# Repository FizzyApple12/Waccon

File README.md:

# Waccon

This repo is right now still a work in progress, nothing has been finalized and things will probably be broken, stay tuned as things are finalized though!

If you'd like to test out the current firmware on your own hardware, there are 2 github actions scripts for the Touch Panel firmware and the Protocol Translator firmware

The 6 Touch Panel firmware builds correspond to which position you want the Touch Panel to be in (1 being top, 6 being bottom)

The 4 Protocol Translator firmware builds correspond to if the translator is controlling the left or right of the controller and if you want to mirror Touch Panel 1's inputs to all 6 Touch Panels

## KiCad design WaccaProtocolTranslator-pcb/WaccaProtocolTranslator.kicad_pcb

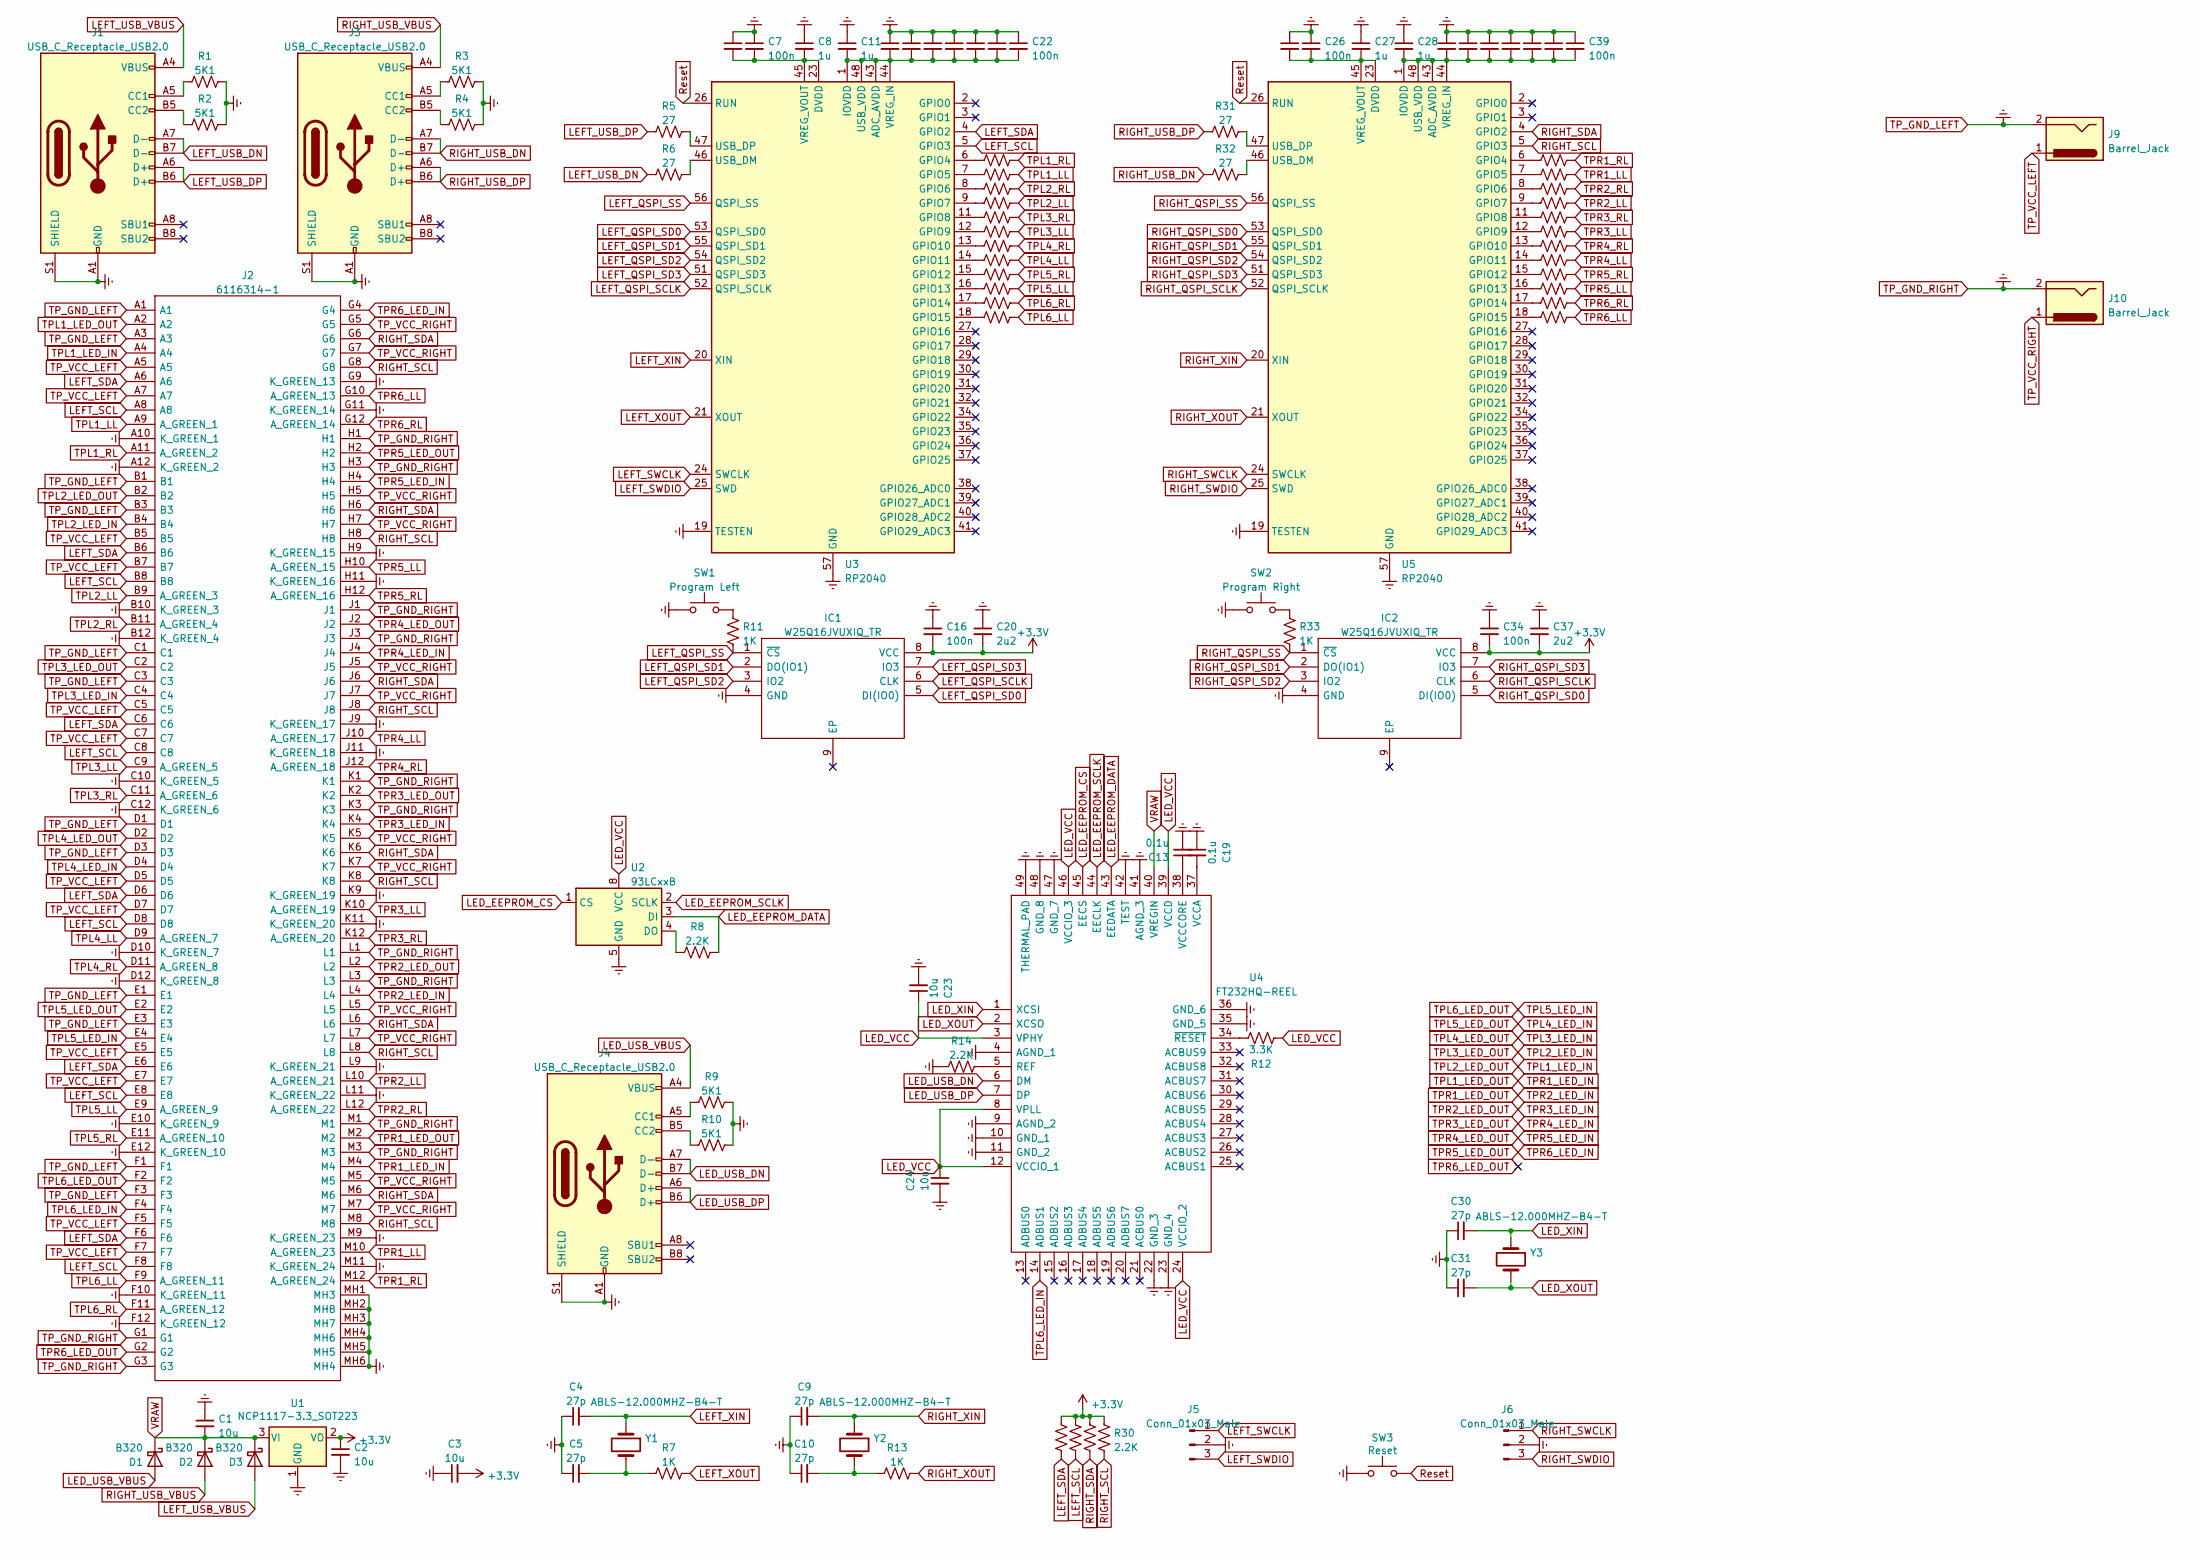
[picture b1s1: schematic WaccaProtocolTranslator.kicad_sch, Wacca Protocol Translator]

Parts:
C1, C2, C3, C23, C24: 10u; C_0402_1005Metric
C4, C5, C9, C10, C30, C31: 27p; C_0402_1005Metric
C6, C7, C12, C14, C15, C16, C17, C18, C21, C22, C25, C26, C29, C32, C33, C34, C35, C36, C38, C39: 100n; C_0402_1005Metric
C8, C11, C27, C28: 1u; C_0402_1005Metric
C13, C19: 0.1u; C_0402_1005Metric
C20, C37: 2u2; C_0402_1005Metric
D1, D2, D3: B320; D_SMC
IC1, IC2: W25Q16JVUXIQ_TR; SON50P300X200X60-9N; Manufacturer_Part_Number W25Q16JVUXIQ TR; Mouser Part Number 454-W25Q16JVUXIQTR
J1, J3, J4: USB_C_Receptacle_USB2.0; USB_C_Receptacle_Amphenol_12401548E4-2A
J2: 6116314-1; 61163141; Mouser Part Number 571-6116314-1
J5, J6: Conn_01x03_Male; PinHeader_1x03_P2.54mm_Vertical
J9, J10: Barrel_Jack; BarrelJack_CUI_PJ-063AH_Horizontal
R1, R2, R3, R4, R9, R10: 5K1; R_0402_1005Metric
R5, R6, R31, R32: 27; R_0402_1005Metric
R7, R11, R13, R33: 1K; R_0402_1005Metric
R8, R14, R27, R28, R29, R30: 2.2K; R_0402_1005Metric
R12: 3.3K; R_0402_1005Metric
R15, R16, R17, R18, R19, R20, R21, R22, R23, R24, R25, R26, R34, R35, R36, R37, R38, R39, R40, R41, R42, R43, R44, R45: 150; R_0402_1005Metric
SW1: Program Left; SW_SPST_B3U-1000P
SW2: Program Right; SW_SPST_B3U-1000P
SW3: Reset; SW_SPST_B3U-1000P
U1: NCP1117-3.3_SOT223; SOT-223-3_TabPin2
U2: 93LCxxB; SOP65P490X110-8N
U3, U5: RP2040; QFN-56-1EP_7x7mm_P0.4mm_EP3.2x3.2mm
U4: FT232HQ-REEL; QFN50P800X800X100-49N-D; Mouser Part Number 895-FT232HQ-REEL
Y1, Y2, Y3: ABLS-12.000MHZ-B4-T; Crystal_HC49-4H_Vertical

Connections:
+3.3V: C2.1, C3.2, C16.2, C20.2, C34.2, C37.2, IC1.8 (VCC), IC2.8 (VCC), R27.2, R28.2, R29.2, R30.2, U1.2 (VO)
LED_EEPROM_CS: U2.1 (CS), U4.45 (EECS)
LED_EEPROM_DATA: R8.2, U2.3 (DI), U4.43 (EEDATA)
LED_EEPROM_SCLK: U2.2 (SCLK), U4.44 (EECLK)
LED_USB_DN: J4.A7 (D-), J4.B7 (D-), U4.6 (DM)
LED_USB_DP: J4.A6 (D+), J4.B6 (D+), U4.7 (DP)
LED_USB_VBUS: D1.2 (A), J4.A4 (VBUS), J4.A9 (VBUS), J4.B4 (VBUS), J4.B9 (VBUS)
LED_VCC: C23.1, C24.1, R12.1, U2.8 (VCC), U4.3 (VPHY), U4.8 (VPLL), U4.12 (VCCIO_1), U4.24 (VCCIO_2), U4.39 (VCCD), U4.46 (VCCIO_3)
LED_XIN: C30.2, U4.1 (XCSI), Y3.1
LED_XOUT: C31.2, U4.2 (XCSO), Y3.2
LEFT_QSPI_SCLK: IC1.6 (CLK), U3.52 (QSPI_SCLK)
LEFT_QSPI_SD0: IC1.5 (DI(IO0)), U3.53 (QSPI_SD0)
LEFT_QSPI_SD1: IC1.2 (DO(IO1)), U3.55 (QSPI_SD1)
LEFT_QSPI_SD2: IC1.3 (IO2), U3.54 (QSPI_SD2)
LEFT_QSPI_SD3: IC1.7 (IO3), U3.51 (QSPI_SD3)
LEFT_QSPI_SS: IC1.1 (~CS), R11.2, U3.56 (QSPI_SS)
LEFT_SCL: J2.A8, J2.B8, J2.C8, J2.D8, J2.E8, J2.F8, R28.1, U3.5 (GPIO3)
LEFT_SDA: J2.A6, J2.B6, J2.C6, J2.D6, J2.E6, J2.F6, R27.1, U3.4 (GPIO2)
LEFT_SWCLK: J5.1, U3.24 (SWCLK)
LEFT_SWDIO: J5.3, U3.25 (SWD)
LEFT_USB_DN: J1.A7 (D-), J1.B7 (D-), R6.1
LEFT_USB_DP: J1.A6 (D+), J1.B6 (D+), R5.1
LEFT_USB_VBUS: D3.2 (A), J1.A4 (VBUS), J1.A9 (VBUS), J1.B4 (VBUS), J1.B9 (VBUS)
LEFT_XIN: C4.2, U3.20 (XIN), Y1.1
LEFT_XOUT: R7.2, U3.21 (XOUT)
unnamed: C5.2, R7.1, Y1.2
unnamed: C10.2, R13.1, Y2.2
unnamed: J1.A5 (CC1), R1.1
unnamed: J1.B5 (CC2), R2.1
unnamed: J3.A5 (CC1), R3.1
unnamed: J3.B5 (CC2), R4.1
unnamed: J4.A5 (CC1), R9.1
unnamed: J4.B5 (CC2), R10.1
unnamed: R11.1, SW1.2
unnamed: R33.1, SW2.2
unnamed: R8.1, U2.4 (DO)
unnamed: C11.2, C12.2, C14.2, C15.2, C17.2, C18.2, C21.2, C22.2, U3.1 (IOVDD), U3.10 (IOVDD), U3.22 (IOVDD), U3.33 (IOVDD), U3.42 (IOVDD), U3.43 (ADC_AVDD), U3.44 (VREG_IN), U3.48 (USB_VDD), U3.49 (IOVDD)
unnamed: R16.1, U3.6 (GPIO4)
unnamed: R15.1, U3.7 (GPIO5)
unnamed: R18.1, U3.8 (GPIO6)
unnamed: R17.1, U3.9 (GPIO7)
unnamed: R20.1, U3.11 (GPIO8)
unnamed: R19.1, U3.12 (GPIO9)
unnamed: R22.1, U3.13 (GPIO10)
unnamed: R21.1, U3.14 (GPIO11)
unnamed: R24.1, U3.15 (GPIO12)
unnamed: R23.1, U3.16 (GPIO13)
unnamed: R26.1, U3.17 (GPIO14)
unnamed: R25.1, U3.18 (GPIO15)
unnamed: R6.2, U3.46 (USB_DM)
unnamed: R5.2, U3.47 (USB_DP)
unnamed: C6.2, C7.2, C8.2, U3.23 (DVDD), U3.45 (VREG_VOUT), U3.50 (DVDD)
unnamed: R14.2, U4.5 (REF)
unnamed: C19.2, U4.37 (VCCA)
unnamed: C13.1, U4.38 (VCCCORE)
unnamed: R12.2, U4.34 (~RESET)
unnamed: C28.2, C29.2, C32.2, C33.2, C35.2, C36.2, C38.2, C39.2, U5.1 (IOVDD), U5.10 (IOVDD), U5.22 (IOVDD), U5.33 (IOVDD), U5.42 (IOVDD), U5.43 (ADC_AVDD), U5.44 (VREG_IN), U5.48 (USB_VDD), U5.49 (IOVDD)
unnamed: R35.1, U5.6 (GPIO4)
unnamed: R34.1, U5.7 (GPIO5)
unnamed: R37.1, U5.8 (GPIO6)
unnamed: R36.1, U5.9 (GPIO7)
unnamed: R39.1, U5.11 (GPIO8)
unnamed: R38.1, U5.12 (GPIO9)
unnamed: R41.1, U5.13 (GPIO10)
unnamed: R40.1, U5.14 (GPIO11)
unnamed: R43.1, U5.15 (GPIO12)
unnamed: R42.1, U5.16 (GPIO13)
unnamed: R45.1, U5.17 (GPIO14)
unnamed: R44.1, U5.18 (GPIO15)
unnamed: R32.2, U5.46 (USB_DM)
unnamed: R31.2, U5.47 (USB_DP)
unnamed: C25.2, C26.2, C27.2, U5.23 (DVDD), U5.45 (VREG_VOUT), U5.50 (DVDD)
RIGHT_QSPI_SCLK: IC2.6 (CLK), U5.52 (QSPI_SCLK)
RIGHT_QSPI_SD0: IC2.5 (DI(IO0)), U5.53 (QSPI_SD0)
RIGHT_QSPI_SD1: IC2.2 (DO(IO1)), U5.55 (QSPI_SD1)
RIGHT_QSPI_SD2: IC2.3 (IO2), U5.54 (QSPI_SD2)
RIGHT_QSPI_SD3: IC2.7 (IO3), U5.51 (QSPI_SD3)
RIGHT_QSPI_SS: IC2.1 (~CS), R33.2, U5.56 (QSPI_SS)
RIGHT_SCL: J2.G8, J2.H8, J2.J8, J2.K8, J2.L8, J2.M8, R30.1, U5.5 (GPIO3)
RIGHT_SDA: J2.G6, J2.H6, J2.J6, J2.K6, J2.L6, J2.M6, R29.1, U5.4 (GPIO2)
RIGHT_SWCLK: J6.1, U5.24 (SWCLK)
RIGHT_SWDIO: J6.3, U5.25 (SWD)
RIGHT_USB_DN: J3.A7 (D-), J3.B7 (D-), R32.1
RIGHT_USB_DP: J3.A6 (D+), J3.B6 (D+), R31.1
RIGHT_USB_VBUS: D2.2 (A), J3.A4 (VBUS), J3.A9 (VBUS), J3.B4 (VBUS), J3.B9 (VBUS)
RIGHT_XIN: C9.2, U5.20 (XIN), Y2.1
RIGHT_XOUT: R13.2, U5.21 (XOUT)
Reset: SW3.2, U3.26 (RUN), U5.26 (RUN)
TPL1_LED_IN: J2.A4, J2.B2
TPL1_LED_OUT: J2.A2, J2.M4
TPL1_LL: J2.A9 (A_GREEN_1), R15.2
TPL1_RL: J2.A11 (A_GREEN_2), R16.2
TPL2_LED_IN: J2.B4, J2.C2
TPL2_LL: J2.B9 (A_GREEN_3), R17.2
TPL2_RL: J2.B11 (A_GREEN_4), R18.2
TPL3_LED_IN: J2.C4, J2.D2
TPL3_LL: J2.C9 (A_GREEN_5), R19.2
TPL3_RL: J2.C11 (A_GREEN_6), R20.2
TPL4_LED_IN: J2.D4, J2.E2
TPL4_LL: J2.D9 (A_GREEN_7), R21.2
TPL4_RL: J2.D11 (A_GREEN_8), R22.2
TPL5_LED_IN: J2.E4, J2.F2
TPL5_LL: J2.E9 (A_GREEN_9), R23.2
TPL5_RL: J2.E11 (A_GREEN_10), R24.2
TPL6_LED_IN: J2.F4, U4.14 (ADBUS1)
TPL6_LL: J2.F9 (A_GREEN_11), R25.2
TPL6_RL: J2.F11 (A_GREEN_12), R26.2
TPR1_LED_OUT: J2.L4, J2.M2
TPR1_LL: J2.M10 (A_GREEN_23), R34.2
TPR1_RL: J2.M12 (A_GREEN_24), R35.2
TPR2_LED_OUT: J2.K4, J2.L2
TPR2_LL: J2.L10 (A_GREEN_21), R36.2
TPR2_RL: J2.L12 (A_GREEN_22), R37.2
TPR3_LED_OUT: J2.J4, J2.K2
TPR3_LL: J2.K10 (A_GREEN_19), R38.2
TPR3_RL: J2.K12 (A_GREEN_20), R39.2
TPR4_LED_OUT: J2.H4, J2.J2
TPR4_LL: J2.J10 (A_GREEN_17), R40.2
TPR4_RL: J2.J12 (A_GREEN_18), R41.2
TPR5_LED_OUT: J2.G4, J2.H2
TPR5_LL: J2.H10 (A_GREEN_15), R42.2
TPR5_RL: J2.H12 (A_GREEN_16), R43.2
TPR6_LED_OUT: J2.G2
TPR6_LL: J2.G10 (A_GREEN_13), R44.2
TPR6_RL: J2.G12 (A_GREEN_14), R45.2
TP_GND_LEFT: C1.1, C2.2, C3.1, C4.1, C5.1, C6.1, C7.1, C8.1, C9.1, C10.1, C11.1, C12.1, C13.2, C14.1, C15.1, C16.1, C17.1, C18.1, C19.1, C20.1, C21.1, C22.1, C23.2, C24.2, C25.1, C26.1, C27.1, C28.1, C29.1, C30.1, C31.1, C32.1, C33.1, C34.1, C35.1, C36.1, C37.1, C38.1, C39.1, IC1.4 (GND), IC2.4 (GND), J1.A1 (GND), J1.A12 (GND), J1.B1 (GND), J1.B12 (GND), J1.S1 (SHIELD), J2.A1, J2.A3, J2.A10 (K_GREEN_1), J2.A12 (K_GREEN_2), J2.B1, J2.B3, J2.B10 (K_GREEN_3), J2.B12 (K_GREEN_4), J2.C1, J2.C3, J2.C10 (K_GREEN_5), J2.C12 (K_GREEN_6), J2.D1, J2.D3, J2.D10 (K_GREEN_7), J2.D12 (K_GREEN_8), J2.E1, J2.E3, J2.E10 (K_GREEN_9), J2.E12 (K_GREEN_10), J2.F1, J2.F3, J2.F10 (K_GREEN_11), J2.F12 (K_GREEN_12), J2.G1, J2.G3, J2.G9 (K_GREEN_13), J2.G11 (K_GREEN_14), J2.H1, J2.H3, J2.H9 (K_GREEN_15), J2.H11 (K_GREEN_16), J2.J1, J2.J3, J2.J9 (K_GREEN_17), J2.J11 (K_GREEN_18), J2.K1, J2.K3, J2.K9 (K_GREEN_19), J2.K11 (K_GREEN_20), J2.L1, J2.L3, J2.L9 (K_GREEN_21), J2.L11 (K_GREEN_22), J2.M1, J2.M3, J2.M9 (K_GREEN_23), J2.M11 (K_GREEN_24), J2.MH1 (MH3), J2.MH2 (MH8), J2.MH3 (MH7), J2.MH4 (MH6), J2.MH5, J2.MH6 (MH4), J3.A1 (GND), J3.A12 (GND), J3.B1 (GND), J3.B12 (GND), J3.S1 (SHIELD), J4.A1 (GND), J4.A12 (GND), J4.B1 (GND), J4.B12 (GND), J4.S1 (SHIELD), J5.2, J6.2, J9.2, J10.2, R1.2, R2.2, R3.2, R4.2, R9.2, R10.2, R14.1, SW1.1, SW2.1, SW3.1, U1.1 (GND), U2.5 (GND), U3.19 (TESTEN), U3.57 (GND), U4.4 (AGND_1), U4.9 (AGND_2), U4.10 (GND_1), U4.11 (GND_2), U4.22 (GND_3), U4.23 (GND_4), U4.35 (GND_5), U4.36 (GND_6), U4.41 (AGND_3), U4.42 (TEST), U4.47 (GND_7), U4.48 (GND_8), U4.49 (THERMAL_PAD), U5.19 (TESTEN), U5.57 (GND)
TP_VCC_LEFT: J2.A5, J2.A7, J2.B5, J2.B7, J2.C5, J2.C7, J2.D5, J2.D7, J2.E5, J2.E7, J2.F5, J2.F7, J9.1
TP_VCC_RIGHT: J2.G5, J2.G7, J2.H5, J2.H7, J2.J5, J2.J7, J2.K5, J2.K7, J2.L5, J2.L7, J2.M5, J2.M7, J10.1
VRAW: C1.2, D1.1 (K), D2.1 (K), D3.1 (K), U1.3 (VI), U4.40 (VREGIN)

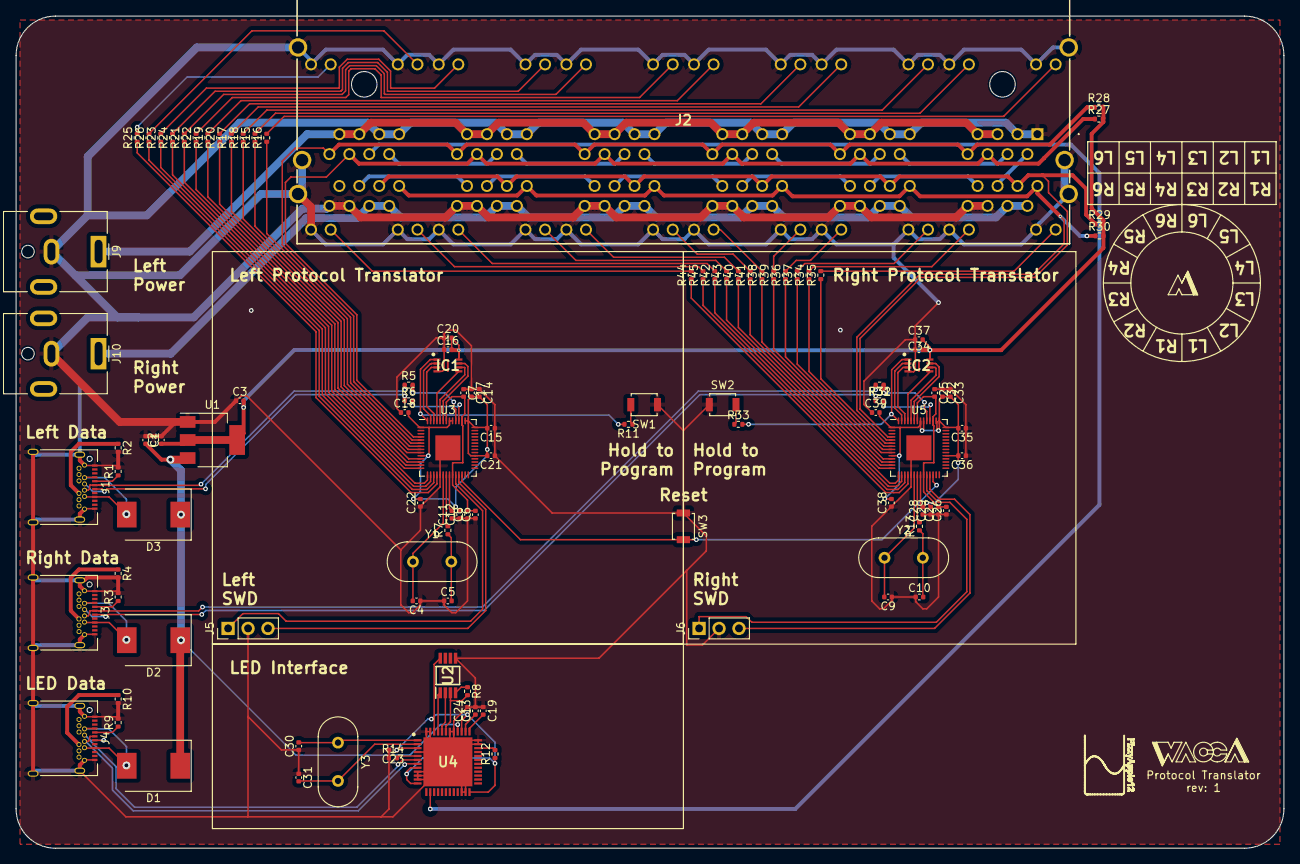
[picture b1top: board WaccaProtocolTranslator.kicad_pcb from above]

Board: 2 copper layers, 161.5 x 106.0 mm, 108 parts (0 on the bottom side), 128 nets.

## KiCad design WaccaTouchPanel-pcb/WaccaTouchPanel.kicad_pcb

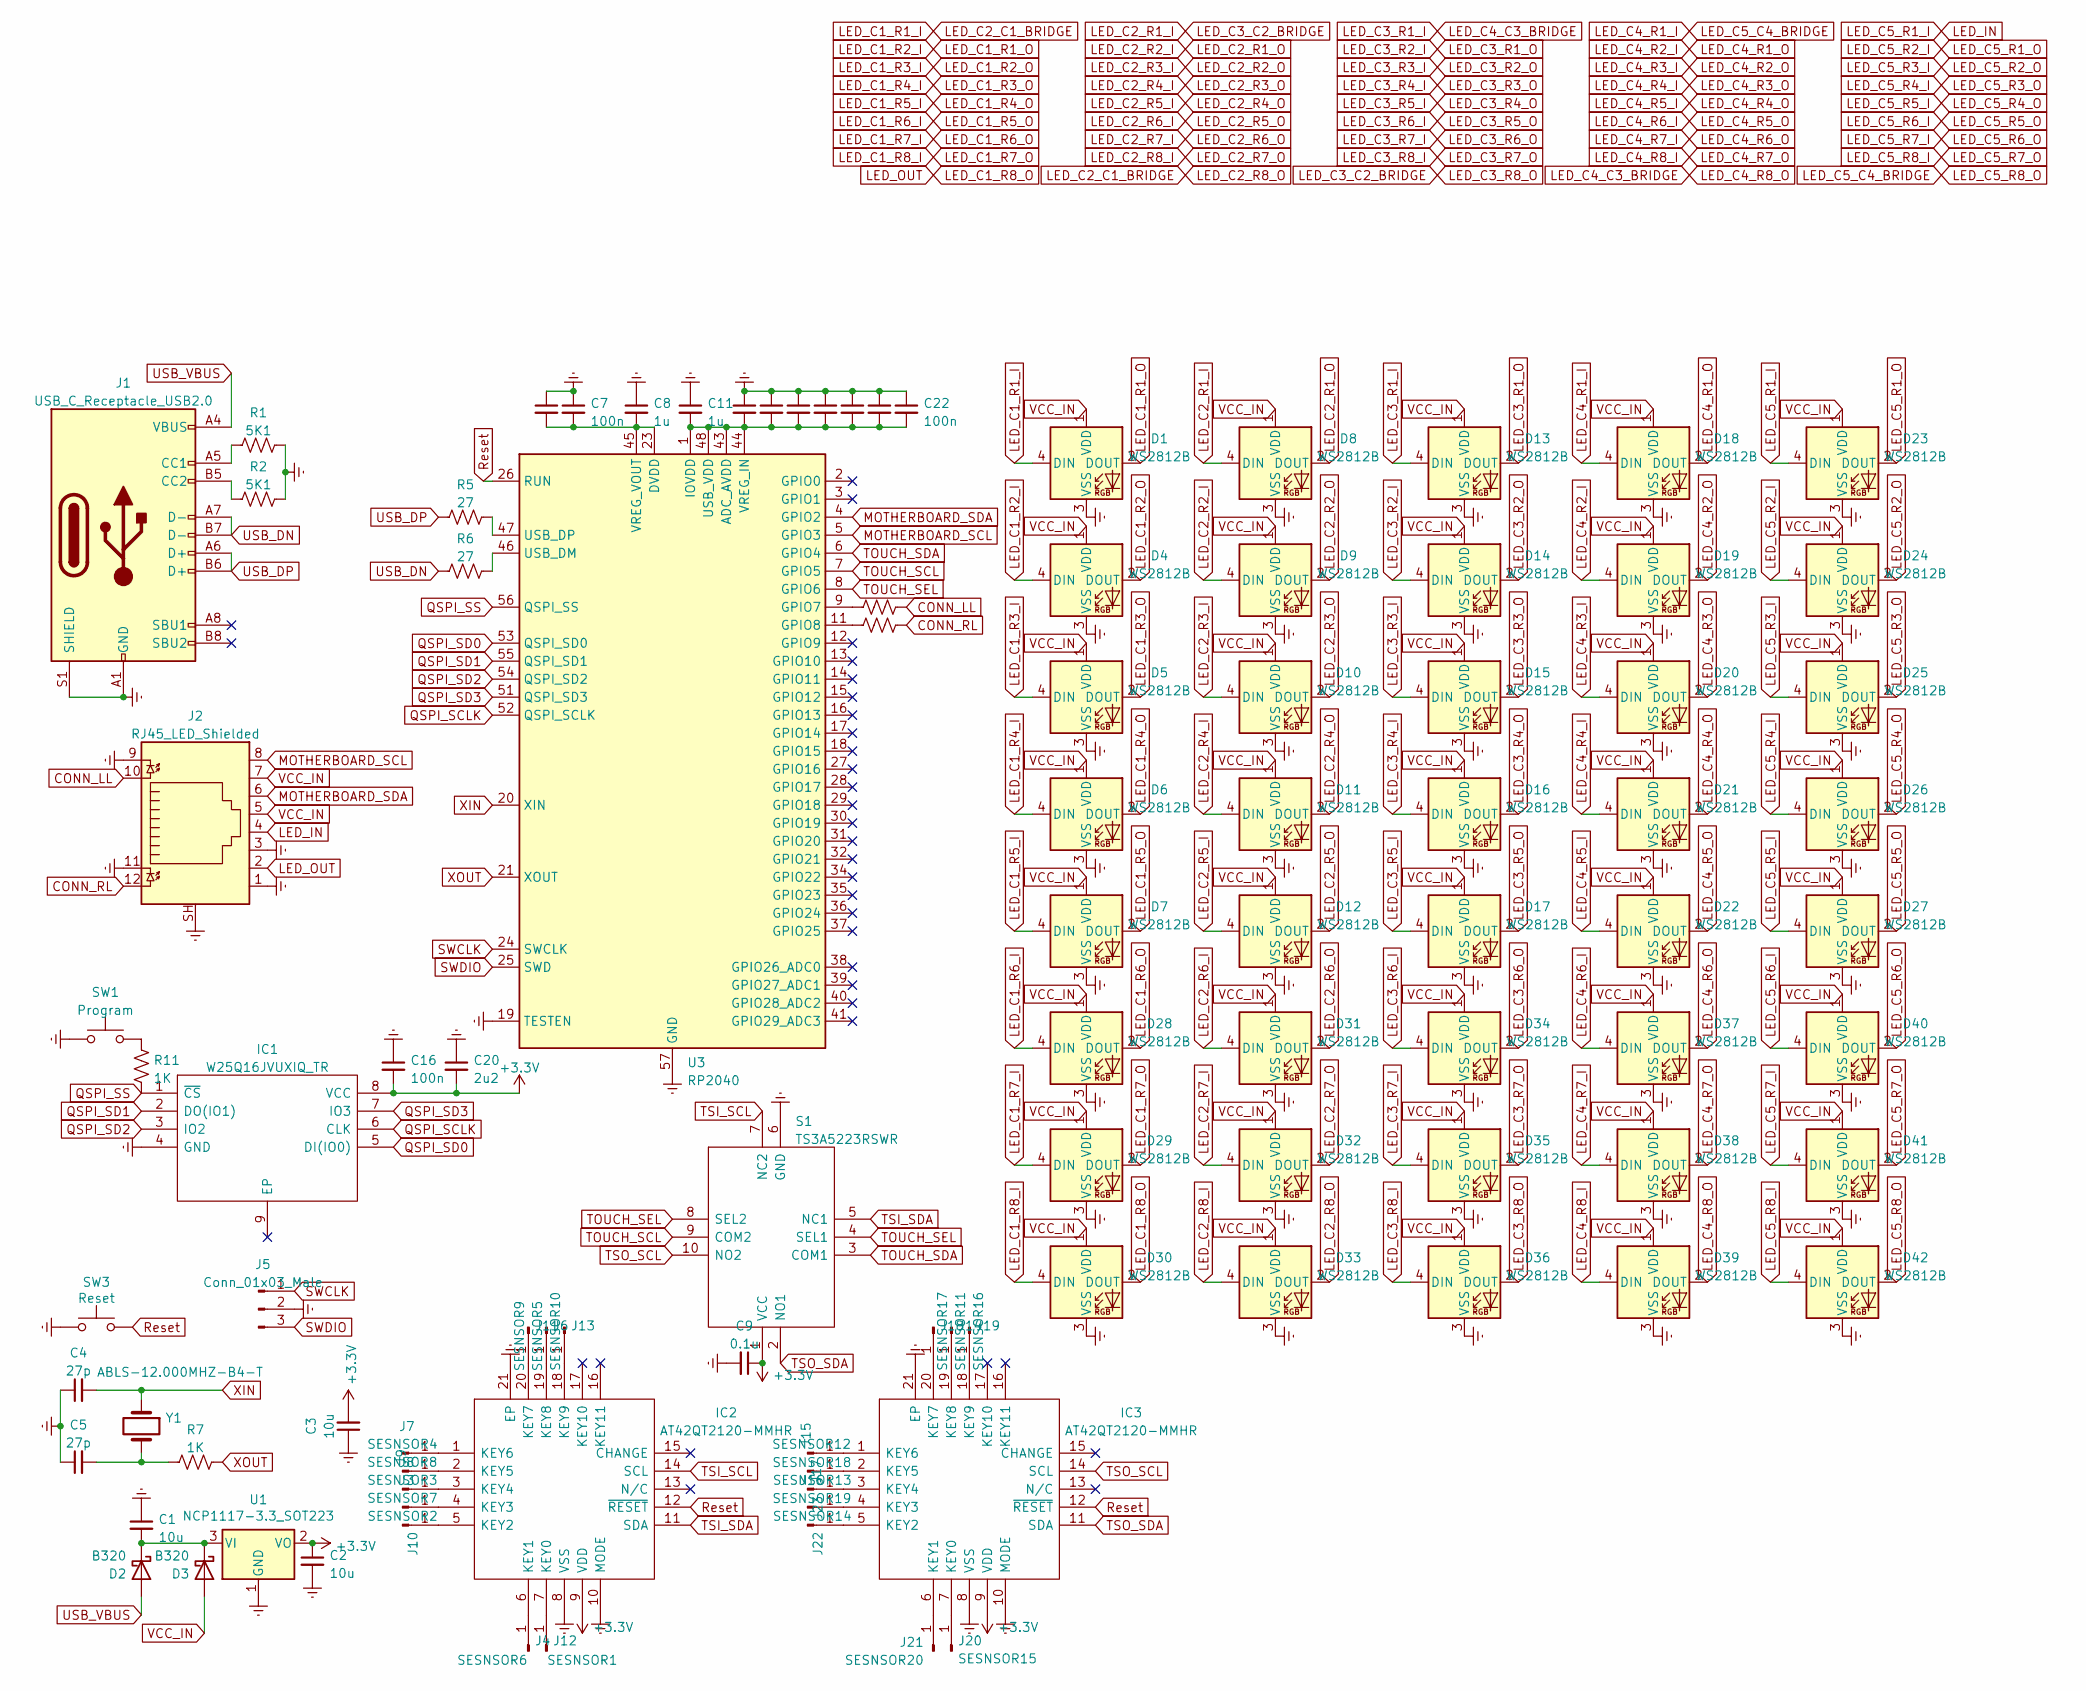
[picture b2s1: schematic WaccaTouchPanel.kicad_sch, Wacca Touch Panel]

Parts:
C1, C2, C3: 10u; C_0402_1005Metric
C4, C5: 27p; C_0402_1005Metric
C6, C7, C12, C14, C15, C16, C17, C18, C21, C22: 100n; C_0402_1005Metric
C8, C11: 1u; C_0402_1005Metric
C9: 0.1u; C_0402_1005Metric
C20: 2u2; C_0402_1005Metric
D1, D4, D5, D6, D7, D8, D9, D10, D11, D12, D13, D14, D15, D16, D17, D18, D19, D20, D21, D22, D23, D24, D25, D26, D27, D28, D29, D30, D31, D32, D33, D34, D35, D36, D37, D38, D39, D40, D41, D42: WS2812B; LED_WS2812B_PLCC4_5.0x5.0mm_P3.2mm
D2, D3: B320; D_SMC
IC1: W25Q16JVUXIQ_TR; SON50P300X200X60-9N; Manufacturer_Part_Number W25Q16JVUXIQ TR; Mouser Part Number 454-W25Q16JVUXIQTR
IC2, IC3: AT42QT2120-MMHR; QFN45P300X300X85-21N; Mouser Part Number 556-AT42QT2120-MMHR
J1: USB_C_Receptacle_USB2.0; USB_C_Receptacle_Amphenol_12401548E4-2A
J2: RJ45_LED_Shielded; RJ45_Amphenol_RJHSE538X
J3: SESNSOR7; PinHeader_1x01_P2.54mm_Vertical
J4: SESNSOR6; PinHeader_1x01_P2.54mm_Vertical
J5: Conn_01x03_Male; PinHeader_1x03_P2.54mm_Vertical
J6: SESNSOR5; PinHeader_1x01_P2.54mm_Vertical
J7: SESNSOR4; PinHeader_1x01_P2.54mm_Vertical
J8: SESNSOR3; PinHeader_1x01_P2.54mm_Vertical
J9: SESNSOR8; PinHeader_1x01_P2.54mm_Vertical
J10: SESNSOR2; PinHeader_1x01_P2.54mm_Vertical
J11: SESNSOR9; PinHeader_1x01_P2.54mm_Vertical
J12: SESNSOR1; PinHeader_1x01_P2.54mm_Vertical
J13: SESNSOR10; PinHeader_1x01_P2.54mm_Vertical
J14: SESNSOR11; PinHeader_1x01_P2.54mm_Vertical
J15: SESNSOR12; PinHeader_1x01_P2.54mm_Vertical
J16: SESNSOR19; PinHeader_1x01_P2.54mm_Vertical
J17: SESNSOR18; PinHeader_1x01_P2.54mm_Vertical
J18: SESNSOR17; PinHeader_1x01_P2.54mm_Vertical
J19: SESNSOR16; PinHeader_1x01_P2.54mm_Vertical
J20: SESNSOR15; PinHeader_1x01_P2.54mm_Vertical
J21: SESNSOR20; PinHeader_1x01_P2.54mm_Vertical
J22: SESNSOR14; PinHeader_1x01_P2.54mm_Vertical
J23: SESNSOR13; PinHeader_1x01_P2.54mm_Vertical
R1, R2: 5K1; R_0402_1005Metric
R5, R6: 27; R_0402_1005Metric
R7, R11: 1K; R_0402_1005Metric
R15, R16: 150; R_0402_1005Metric
S1: TS3A5223RSWR; RSW_RPUQFNN10_; Mouser Part Number 595-TS3A5223RSWR
SW1: Program; SW_SPST_B3U-1000P
SW3: Reset; SW_SPST_B3U-1000P
U1: NCP1117-3.3_SOT223; SOT-223-3_TabPin2
U3: RP2040; QFN-56-1EP_7x7mm_P0.4mm_EP3.2x3.2mm
Y1: ABLS-12.000MHZ-B4-T; Crystal_HC49-4H_Vertical

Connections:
+3.3V: C2.1, C3.2, C9.1, C16.2, C20.2, IC1.8 (VCC), IC2.9 (VDD), IC3.9 (VDD), S1.1 (VCC), U1.2 (VO)
CONN_LL: J2.10, R16.2
CONN_RL: J2.12, R15.2
Earth: C1.1, C2.2, C3.1, C4.1, C5.1, C6.1, C7.1, C8.1, C9.2, C11.1, C12.1, C14.1, C15.1, C16.1, C17.1, C18.1, C20.1, C21.1, C22.1, D1.3 (VSS), D4.3 (VSS), D5.3 (VSS), D6.3 (VSS), D7.3 (VSS), D8.3 (VSS), D9.3 (VSS), D10.3 (VSS), D11.3 (VSS), D12.3 (VSS), D13.3 (VSS), D14.3 (VSS), D15.3 (VSS), D16.3 (VSS), D17.3 (VSS), D18.3 (VSS), D19.3 (VSS), D20.3 (VSS), D21.3 (VSS), D22.3 (VSS), D23.3 (VSS), D24.3 (VSS), D25.3 (VSS), D26.3 (VSS), D27.3 (VSS), D28.3 (VSS), D29.3 (VSS), D30.3 (VSS), D31.3 (VSS), D32.3 (VSS), D33.3 (VSS), D34.3 (VSS), D35.3 (VSS), D36.3 (VSS), D37.3 (VSS), D38.3 (VSS), D39.3 (VSS), D40.3 (VSS), D41.3 (VSS), D42.3 (VSS), IC1.4 (GND), IC2.8 (VSS), IC2.10 (MODE), IC2.21 (EP), IC3.8 (VSS), IC3.10 (MODE), IC3.21 (EP), J1.A1 (GND), J1.A12 (GND), J1.B1 (GND), J1.B12 (GND), J1.S1 (SHIELD), J2.1, J2.3, J2.9, J2.11, J2.SH, J5.2, R1.2, R2.2, S1.6 (GND), SW1.1, SW3.1, U1.1 (GND), U3.19 (TESTEN), U3.57 (GND)
LED_C1_R1_I: D1.4 (DIN), D33.2 (DOUT)
LED_C1_R1_O: D1.2 (DOUT), D4.4 (DIN)
LED_C1_R2_O: D4.2 (DOUT), D5.4 (DIN)
LED_C1_R3_O: D5.2 (DOUT), D6.4 (DIN)
LED_C1_R4_O: D6.2 (DOUT), D7.4 (DIN)
LED_C1_R5_O: D7.2 (DOUT), D28.4 (DIN)
LED_C1_R6_O: D28.2 (DOUT), D29.4 (DIN)
LED_C1_R7_O: D29.2 (DOUT), D30.4 (DIN)
LED_C1_R8_O: D30.2 (DOUT), J2.2
LED_C2_R1_O: D8.2 (DOUT), D9.4 (DIN)
LED_C2_R2_O: D9.2 (DOUT), D10.4 (DIN)
LED_C2_R3_O: D10.2 (DOUT), D11.4 (DIN)
LED_C2_R4_O: D11.2 (DOUT), D12.4 (DIN)
LED_C2_R6_I: D12.2 (DOUT), D31.4 (DIN)
LED_C2_R6_O: D31.2 (DOUT), D32.4 (DIN)
LED_C2_R7_O: D32.2 (DOUT), D33.4 (DIN)
LED_C3_R1_I: D13.4 (DIN), D39.2 (DOUT)
LED_C3_R1_O: D13.2 (DOUT), D14.4 (DIN)
LED_C3_R2_O: D14.2 (DOUT), D15.4 (DIN)
LED_C3_R3_O: D15.2 (DOUT), D16.4 (DIN)
LED_C3_R4_O: D16.2 (DOUT), D17.4 (DIN)
LED_C3_R5_O: D17.2 (DOUT), D34.4 (DIN)
LED_C3_R6_O: D34.2 (DOUT), D35.4 (DIN)
LED_C3_R7_O: D35.2 (DOUT), D36.4 (DIN)
LED_C3_R8_O: D8.4 (DIN), D36.2 (DOUT)
LED_C4_R2_I: D18.2 (DOUT), D19.4 (DIN)
LED_C4_R3_I: D19.2 (DOUT), D20.4 (DIN)
LED_C4_R4_I: D20.2 (DOUT), D21.4 (DIN)
LED_C4_R5_I: D21.2 (DOUT), D22.4 (DIN)
LED_C4_R5_O: D22.2 (DOUT), D37.4 (DIN)
LED_C4_R6_O: D37.2 (DOUT), D38.4 (DIN)
LED_C4_R7_O: D38.2 (DOUT), D39.4 (DIN)
LED_C5_R1_I: D23.4 (DIN), J2.4
LED_C5_R2_I: D23.2 (DOUT), D24.4 (DIN)
LED_C5_R3_I: D24.2 (DOUT), D25.4 (DIN)
LED_C5_R4_I: D25.2 (DOUT), D26.4 (DIN)
LED_C5_R5_I: D26.2 (DOUT), D27.4 (DIN)
LED_C5_R5_O: D27.2 (DOUT), D40.4 (DIN)
LED_C5_R6_O: D40.2 (DOUT), D41.4 (DIN)
LED_C5_R7_O: D41.2 (DOUT), D42.4 (DIN)
LED_C5_R8_O: D18.4 (DIN), D42.2 (DOUT)
MOTHERBOARD_SCL: J2.8, U3.5 (GPIO3)
MOTHERBOARD_SDA: J2.6, U3.4 (GPIO2)
unnamed: C1.2, D2.1 (K), D3.1 (K), U1.3 (VI)
unnamed: C5.2, R7.1, Y1.2
unnamed: C6.2, C7.2, C8.2, U3.23 (DVDD), U3.45 (VREG_VOUT), U3.50 (DVDD)
unnamed: C11.2, C12.2, C14.2, C15.2, C17.2, C18.2, C21.2, C22.2, U3.1 (IOVDD), U3.10 (IOVDD), U3.22 (IOVDD), U3.33 (IOVDD), U3.42 (IOVDD), U3.43 (ADC_AVDD), U3.44 (VREG_IN), U3.48 (USB_VDD), U3.49 (IOVDD)
unnamed: IC2.1 (KEY6), J7.1
unnamed: IC2.2 (KEY5), J9.1
unnamed: IC2.3 (KEY4), J8.1
unnamed: IC2.4 (KEY3), J3.1
unnamed: IC2.5 (KEY2), J10.1
unnamed: IC2.6 (KEY1), J4.1
unnamed: IC2.7 (KEY0), J12.1
unnamed: IC2.18 (KEY9), J13.1
unnamed: IC2.19 (KEY8), J6.1
unnamed: IC2.20 (KEY7), J11.1
unnamed: IC3.1 (KEY6), J15.1
unnamed: IC3.2 (KEY5), J17.1
unnamed: IC3.3 (KEY4), J23.1
unnamed: IC3.4 (KEY3), J16.1
unnamed: IC3.5 (KEY2), J22.1
unnamed: IC3.6 (KEY1), J21.1
unnamed: IC3.7 (KEY0), J20.1
unnamed: IC3.18 (KEY9), J19.1
unnamed: IC3.19 (KEY8), J14.1
unnamed: IC3.20 (KEY7), J18.1
unnamed: J1.A5 (CC1), R1.1
unnamed: J1.B5 (CC2), R2.1
unnamed: R5.2, U3.47 (USB_DP)
unnamed: R6.2, U3.46 (USB_DM)
unnamed: R11.1, SW1.2
unnamed: R15.1, U3.11 (GPIO8)
unnamed: R16.1, U3.9 (GPIO7)
QSPI_SCLK: IC1.6 (CLK), U3.52 (QSPI_SCLK)
QSPI_SD0: IC1.5 (DI(IO0)), U3.53 (QSPI_SD0)
QSPI_SD1: IC1.2 (DO(IO1)), U3.55 (QSPI_SD1)
QSPI_SD2: IC1.3 (IO2), U3.54 (QSPI_SD2)
QSPI_SD3: IC1.7 (IO3), U3.51 (QSPI_SD3)
QSPI_SS: IC1.1 (~CS), R11.2, U3.56 (QSPI_SS)
Reset: IC2.12 (~RESET), IC3.12 (~RESET), SW3.2, U3.26 (RUN)
SWCLK: J5.1, U3.24 (SWCLK)
SWDIO: J5.3, U3.25 (SWD)
TOUCH_SCL: S1.9 (COM2), U3.7 (GPIO5)
TOUCH_SDA: S1.3 (COM1), U3.6 (GPIO4)
TOUCH_SEL: S1.4 (SEL1), S1.8 (SEL2), U3.8 (GPIO6)
TSI_SCL: IC2.14 (SCL), S1.7 (NC2)
TSI_SDA: IC2.11 (SDA), S1.5 (NC1)
TSO_SCL: IC3.14 (SCL), S1.10 (NO2)
TSO_SDA: IC3.11 (SDA), S1.2 (NO1)
USB_DN: J1.A7 (D-), J1.B7 (D-), R6.1
USB_DP: J1.A6 (D+), J1.B6 (D+), R5.1
USB_VBUS: D2.2 (A), J1.A4 (VBUS), J1.A9 (VBUS), J1.B4 (VBUS), J1.B9 (VBUS)
VCC_IN: D1.1 (VDD), D3.2 (A), D4.1 (VDD), D5.1 (VDD), D6.1 (VDD), D7.1 (VDD), D8.1 (VDD), D9.1 (VDD), D10.1 (VDD), D11.1 (VDD), D12.1 (VDD), D13.1 (VDD), D14.1 (VDD), D15.1 (VDD), D16.1 (VDD), D17.1 (VDD), D18.1 (VDD), D19.1 (VDD), D20.1 (VDD), D21.1 (VDD), D22.1 (VDD), D23.1 (VDD), D24.1 (VDD), D25.1 (VDD), D26.1 (VDD), D27.1 (VDD), D28.1 (VDD), D29.1 (VDD), D30.1 (VDD), D31.1 (VDD), D32.1 (VDD), D33.1 (VDD), D34.1 (VDD), D35.1 (VDD), D36.1 (VDD), D37.1 (VDD), D38.1 (VDD), D39.1 (VDD), D40.1 (VDD), D41.1 (VDD), D42.1 (VDD), J2.5, J2.7
XIN: C4.2, U3.20 (XIN), Y1.1
XOUT: R7.2, U3.21 (XOUT)

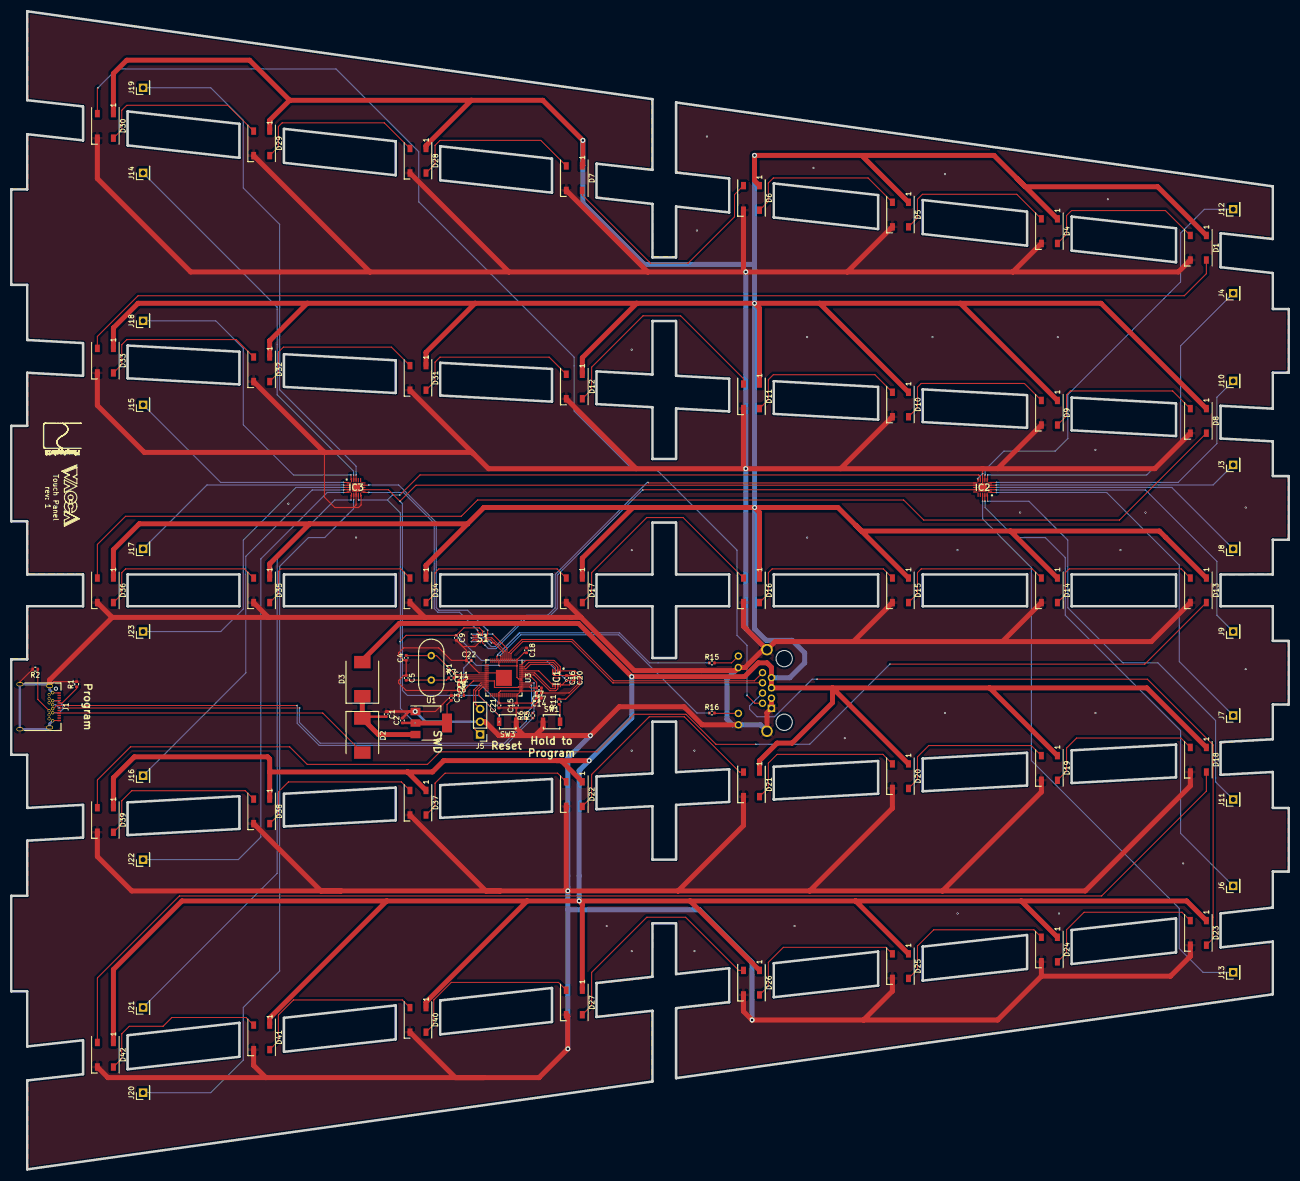
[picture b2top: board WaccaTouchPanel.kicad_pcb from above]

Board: 2 copper layers, 254.9 x 231.1 mm, 101 parts (1 on the bottom side), 100 nets.

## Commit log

2022-07-01 Initial commit with V1 hardware
2022-07-01 Hardware V2
2022-07-01 Hardware V3
2022-07-01 added metadata for my website
2022-07-01 oops forgor to save lmao
2022-07-01 added my block diagram
2022-07-01 removed transparent background
2022-07-02 it's alive! still need to add some serial port and i2c init fixes but other than that this is pretty much ready to go.
2022-07-02 replaced the default pico uart libs with a custom tinyusb-based serial lib
2022-07-02 added actions scripts to automatically build the protocol translator and touch panel firmware on push
2022-07-02 did a pepega formatting error
2022-07-02 More pepega mistakes lmao
2022-07-02 forgor to add a checkout step
2022-07-02 forgot to chmod
2022-07-02 debugging actions
2022-07-02 more debugging
2022-07-02 debugging
2022-07-03 fix for cd
2022-07-03 updated the readme
2022-07-03 fixed error with working-directory
2022-07-03 fix actions not uploading artifact
2022-07-03 merged all actions in to one file
2022-07-03 got to work on the schematic for the Protocol Translator, it's unfinished though
2022-07-05 designed the Protocol Translator PCB and added a PCB build task during production file generation
2022-07-05 fixed github actions yml
2022-07-05 forgot to add KiBot configuration files
2022-07-05 accidental $ in actions file
2022-07-05 added cad generation and changed the an artifact name for clarity
2022-07-05 forgot to add cad config
2022-07-07 Got a ton of work done on the Touch Panel PCB, still need to route the LED traces
2022-07-07 finished Touch Panel PCB and added it to actions
2022-07-07 fixed actions artifact name
2023-08-19 A few changes that needed to be pushed, the power switching circuitry has been removed temporarily to allow for manual power switching. I also baked the FT232HQ connection to the LED bus and changed 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
2023-08-19 update kibot ploting resources
2023-08-19 update kibot to kicad 7
2023-08-19 attempt 2 to fix the pcbdraw style path
2023-08-21 add a picture to the Readme
